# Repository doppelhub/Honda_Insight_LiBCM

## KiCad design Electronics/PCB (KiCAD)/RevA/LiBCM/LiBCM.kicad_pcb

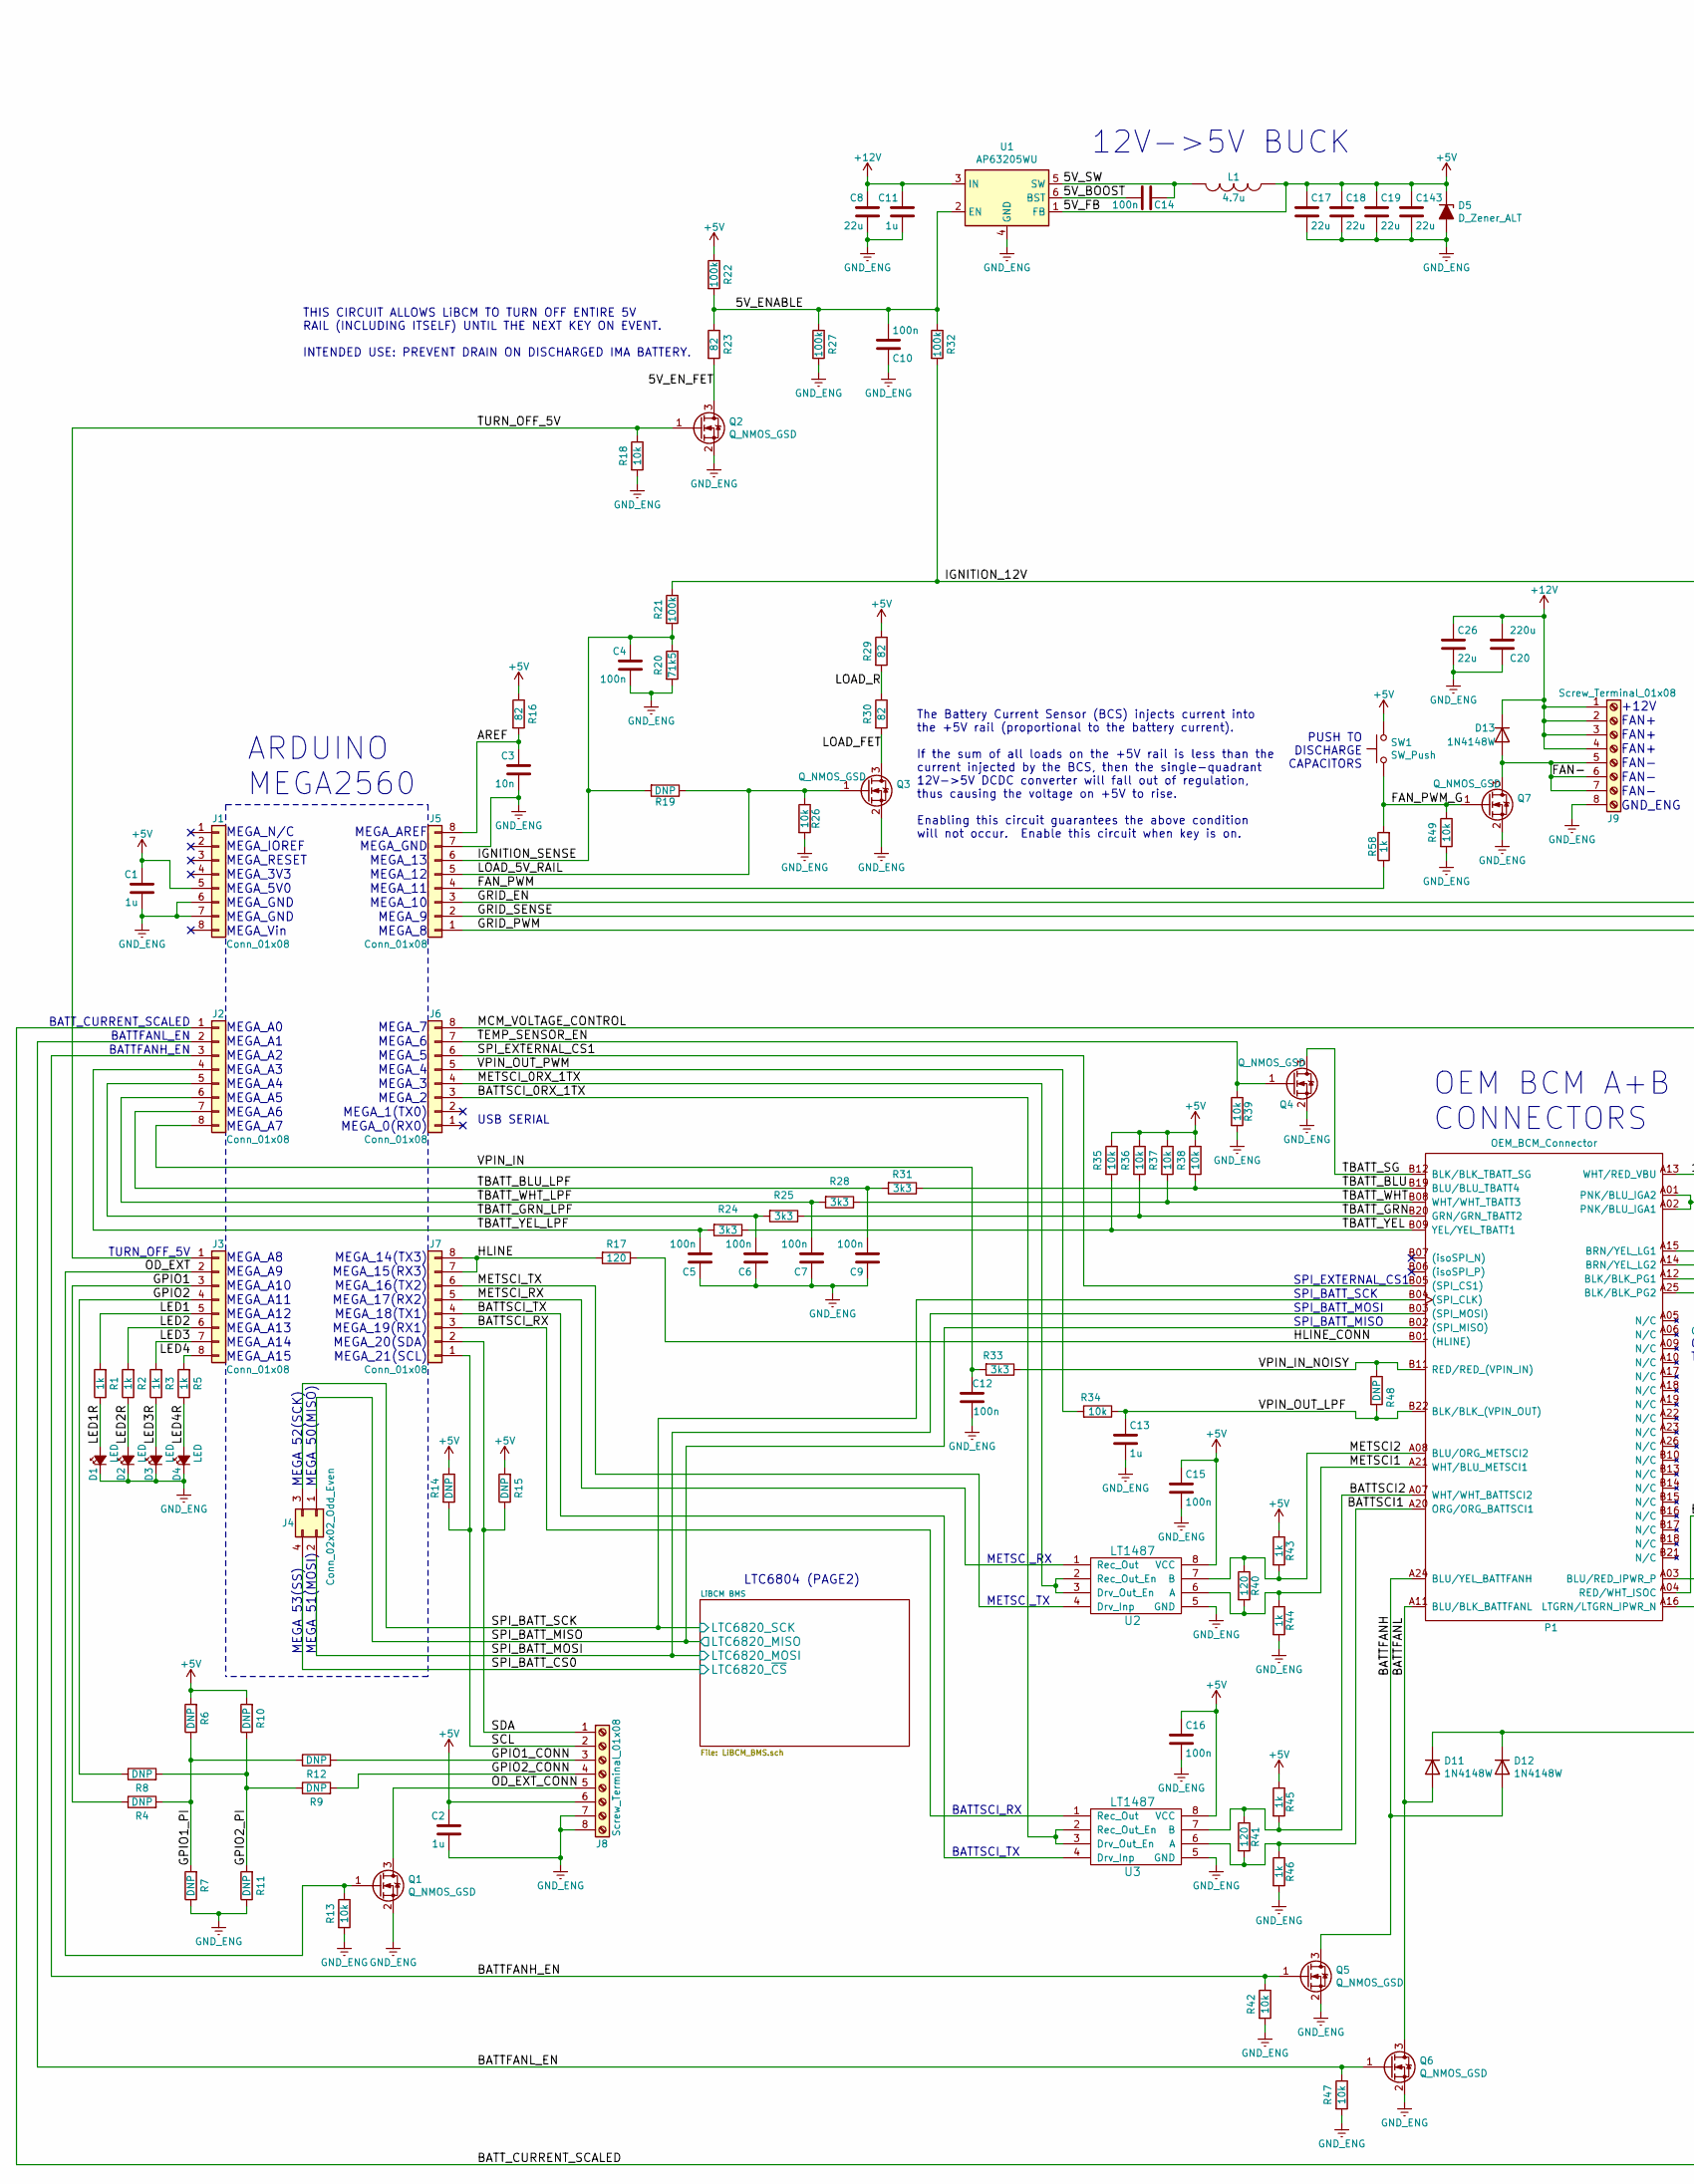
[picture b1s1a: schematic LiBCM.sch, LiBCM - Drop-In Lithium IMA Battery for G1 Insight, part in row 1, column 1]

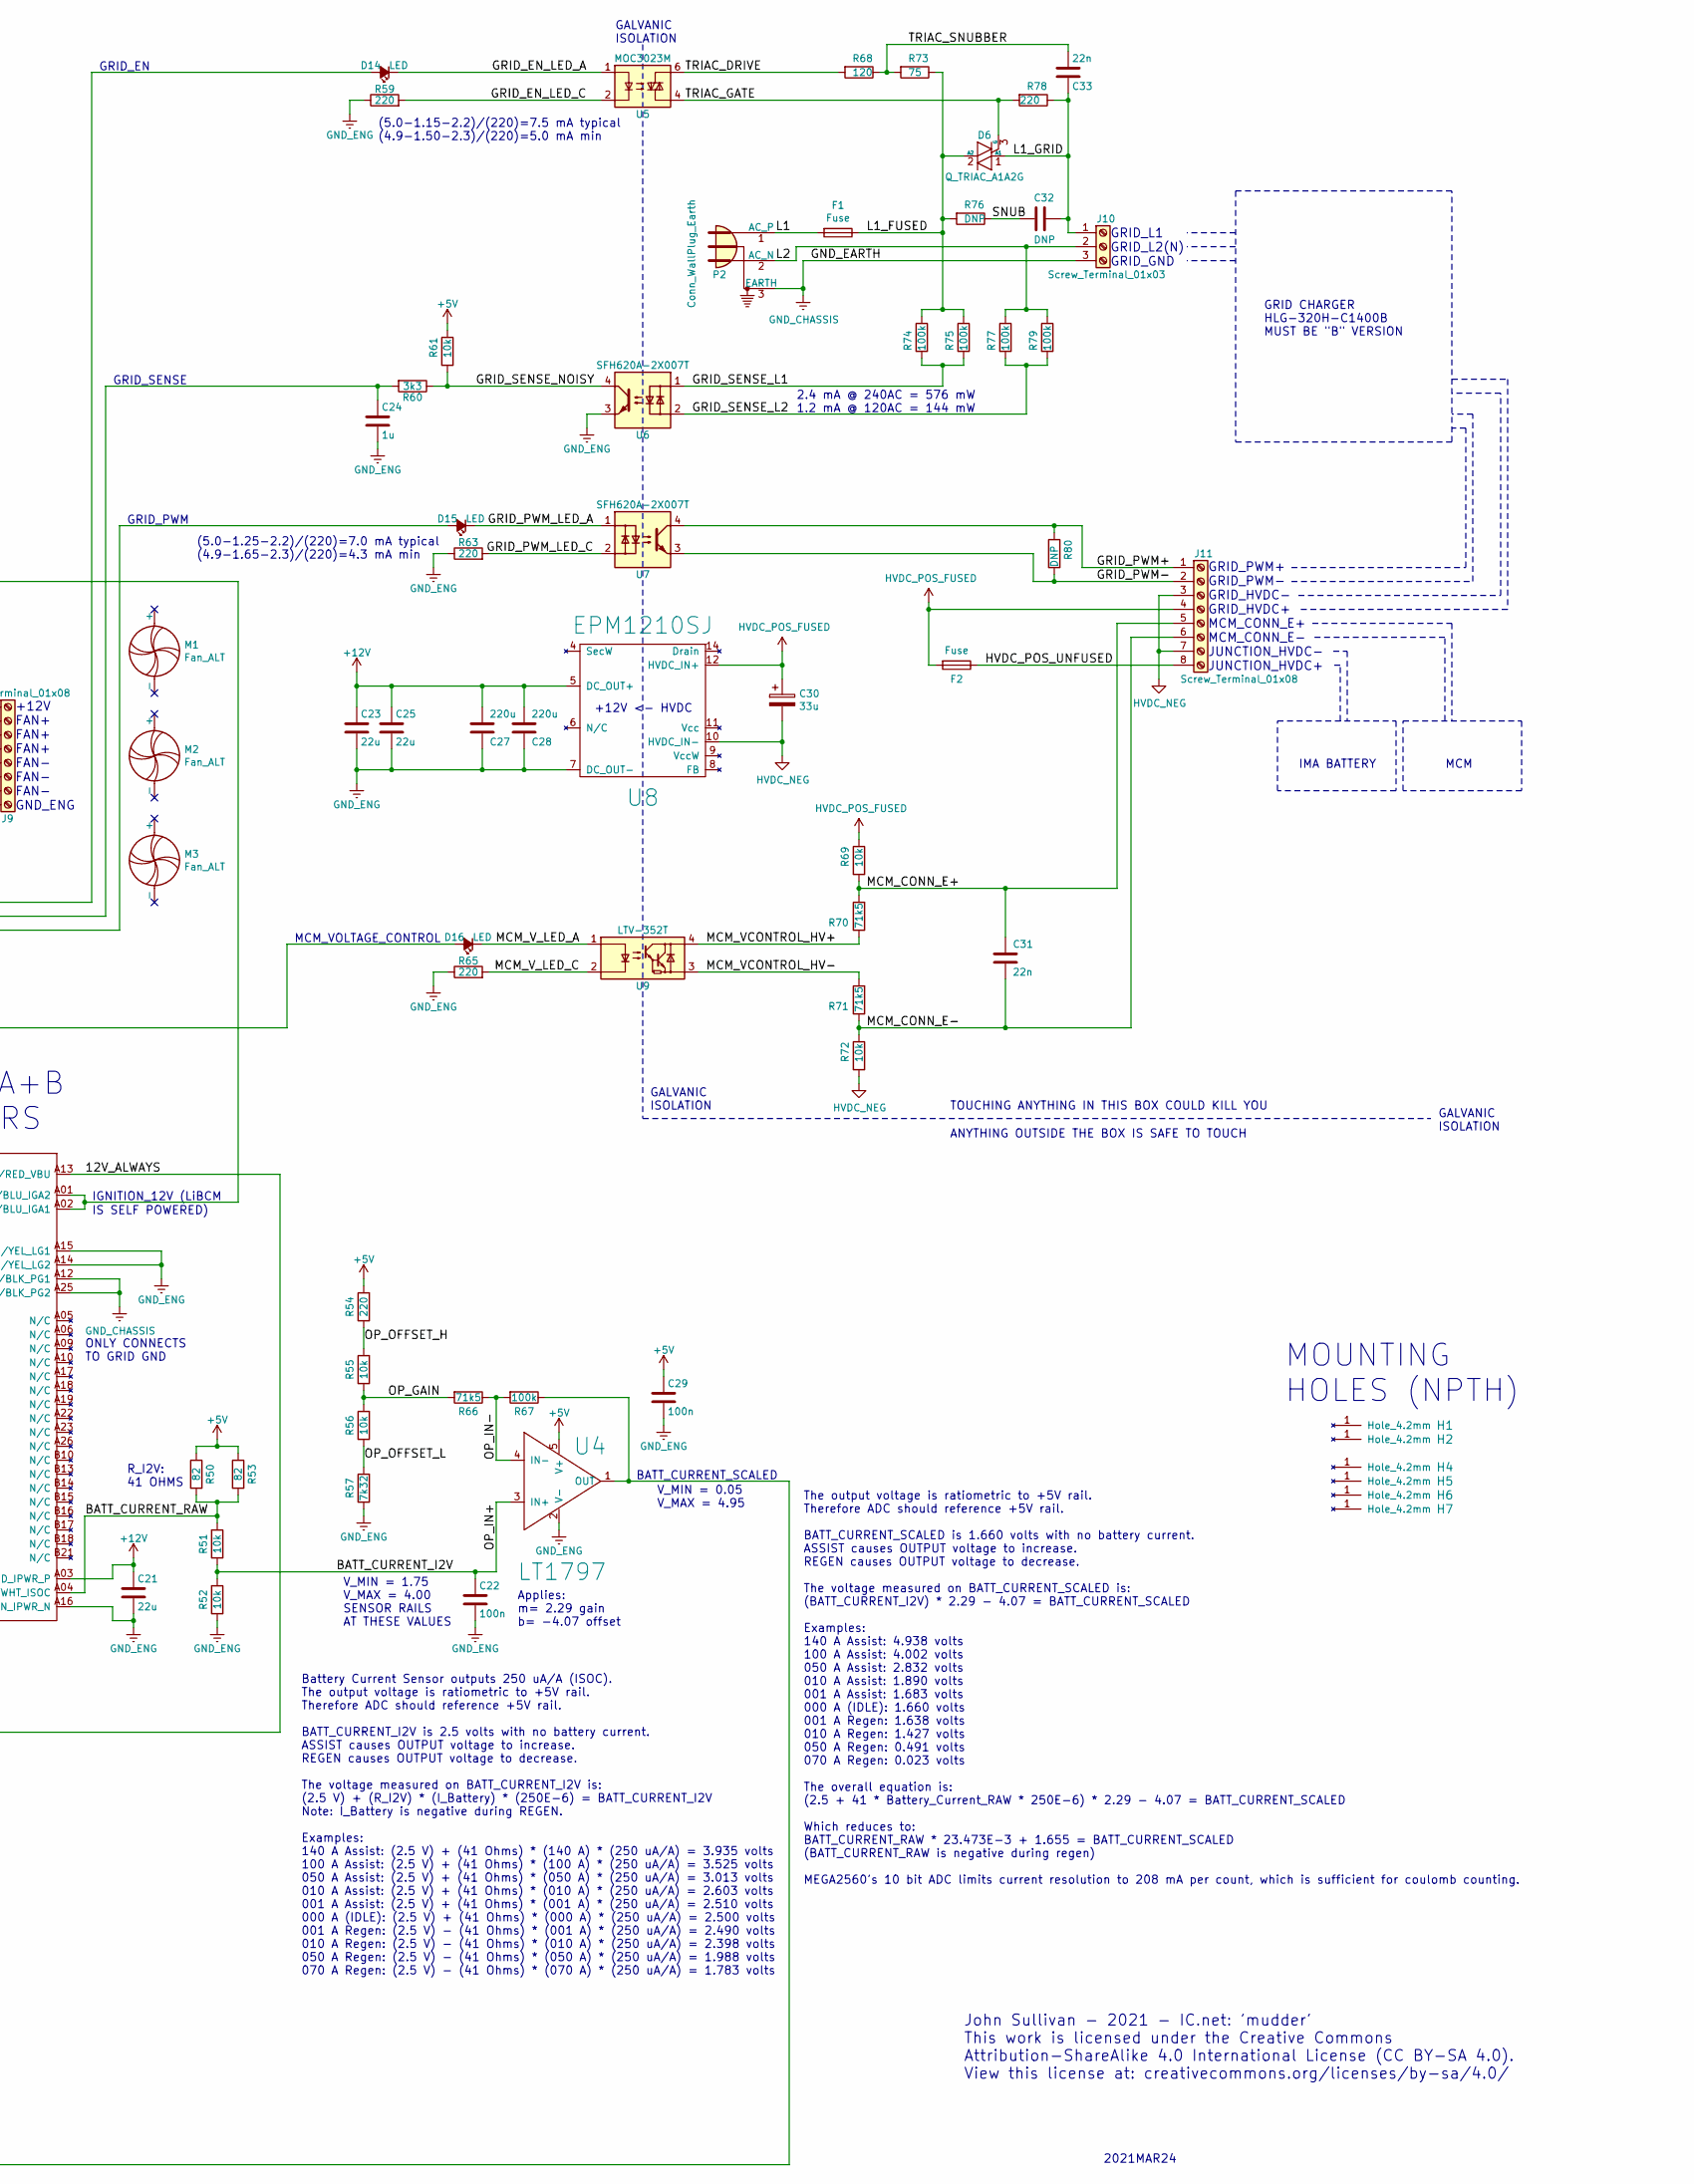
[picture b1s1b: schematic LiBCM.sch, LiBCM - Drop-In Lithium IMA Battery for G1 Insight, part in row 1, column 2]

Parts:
C1, C2, C11, C13, C24: 1u; C_0805_2012Metric
C3: 10n; C_0805_2012Metric
C4, C5, C6, C7, C9, C10, C12, C14, C15, C16, C22, C29: 100n; C_0805_2012Metric
C8, C17, C18, C19, C21, C23, C25, C26, C143: 22u; C_1210_3225Metric
C20, C27, C28: 220u; CP_Elec_10x10
C30: 33u; CP_Radial_D22.0mm_P10.00mm_SnapIn
C31, C33: 22n; C_1206_3216Metric
C32: DNP; C_1206_3216Metric
D1, D2, D3, D4, D14, D15, D16: LED; LED_0805_2012Metric_Castellated
D5: D_Zener_ALT; D_SOD-123
D6: Q_TRIAC_A1A2G; TO-252-3_TabPin2
D11, D12, D13: 1N4148W; D_SOD-123
F1, F2: Fuse; Fuseholder_Cylinder-5x20mm_Schurter_0031_8201_Horizontal_Op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
H1, H2, H4, H5, H6, H7: Hole-4mm2; MountingHole_4.5mm_Pad
J1, J2, J3, J5, J6, J7: Conn_01x08; PinHeader_1x08_P2.54mm_Vertical
J4: Conn_02x02_Odd_Even; PinHeader_2x02_P2.54mm_Vertical
J8, J9, J11: Screw_Terminal_01x08; CONN_1751303
J10: Screw_Terminal_01x03; SolderWire-1sqmm_1x03_P5.4mm_D1.4mm_OD2.7mm
L1: 4.7u; L_TDK_SLF7045
M1, M2, M3: Fan_ALT; FAN_60x60OD_50x50Holes
P1: OEM_BCM_Connector; CONN_BCM_174917-6
P2: Conn_WallPlug_Earth; SolderWire-1sqmm_1x03_P5.4mm_D1.4mm_OD2.7mm
Q1, Q2, Q3, Q4, Q5, Q6, Q7: Q_NMOS_GSD; SOT-23
R1, R2, R3, R5, R43, R44, R45, R46, R58: 1k; R_0805_2012Metric
R4, R6, R7, R8, R9, R10, R11, R12, R14, R15, R19, R48, R80: DNP; R_0805_2012Metric
R13, R18, R26, R34, R35, R36, R37, R38, R39, R42, R47, R49, R51, R52, R55, R56, R61, R69, R72: 10k; R_0805_2012Metric
R16, R23, R29, R30, R50, R53: 82; R_0805_2012Metric
R17, R40, R41, R68: 120; R_0805_2012Metric
R20, R66, R70, R71: 71k5; R_0805_2012Metric
R21, R22, R27, R32, R67, R74, R75, R77, R79: 100k; R_0805_2012Metric
R24, R25, R28, R31, R33, R60: 3k3; R_0805_2012Metric
R54, R59, R63, R65, R78: 220; R_0805_2012Metric
R57: 7k32; R_0805_2012Metric
R73: 75; R_2010_5025Metric
R76: DNP; R_2010_5025Metric
SW1: SW_Push; Panasonic_EVQPUJ_EVQPUA
U1: AP63205WU; TSOT-23-6
U2, U3: LT1487; SOIC-8_5.23x5.23mm_P1.27mm
U4: LT1797; TSOT-23-5
U5: MOC3023M; SMDIP-6_W9.53mm
U6, U7: SFH620A-2X007T; SMDIP-4_W9.53mm_Clearance8mm
U8: EPM1210SJ; DCDC-EPM1210SJ
U9: LTV-352T; SO-4_4.4x3.6mm_P2.54mm

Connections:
+5V: C1.1, C2.1, C15.1, C16.1, C17.1, C18.1, C19.1, C29.1, C143.1, D5.1 (K), J1.5, J8.6, L1.1, R6.2, R10.2, R14.1, R15.2, R16.1, R22.1, R29.1, R35.1, R36.1, R37.1, R38.1, R43.1, R45.1, R50.1, R53.1, R54.2, R61.1, SW1.2, U1.1 (FB), U2.8 (VCC), U3.8 (VCC), U4.5 (V+); also elsewhere on the board
+12V: C8.1, C11.1, C20.1, C21.1, C23.1, C25.1, C26.1, C27.1, C28.1, D13.1 (K), J9.1, J9.2, J9.3, J9.4, P1.A03 (BLU/RED_IPWR_P), U1.3 (IN), U8.5 (DC_OUT+)
/5V_BOOST: C14.2, U1.6 (BST)
/5V_ENABLE: C10.2, R22.2, R23.1, R27.1, R32.1, U1.2 (EN)
/5V_EN_FET: Q2.3 (D), R23.2
/5V_SW: C14.1, L1.2, U1.5 (SW)
/12V_ALWAYS: D11.1 (K), D12.1 (K), P1.A13 (WHT/RED_VBU)
/AREF: C3.1, J5.8, R16.2
/BATTFANH: D12.2 (A), P1.A24 (BLU/YEL_BATTFANH), Q5.3 (D)
/BATTFANH_EN: J2.3, Q5.1 (G), R42.1
/BATTFANL: D11.2 (A), P1.A11 (BLU/BLK_BATTFANL), Q6.3 (D)
/BATTFANL_EN: J2.2, Q6.1 (G), R47.1
/BATTSCI1: P1.A20 (ORG/ORG_BATTSCI1), R41.2, R46.1, U3.6 (A)
/BATTSCI2: P1.A07 (WHT/WHT_BATTSCI2), R41.1, R45.2, U3.7 (B)
/BATTSCI_0RX_1TX: J6.3, U3.2 (Rec_Out_En), U3.3 (Drv_Out_En)
/BATTSCI_RX: J7.3, U3.1 (Rec_Out)
/BATTSCI_TX: J7.4, U3.4 (Drv_Inp)
/BATT_CURRENT_I2V: C22.1, R51.1, R52.2, U4.3 (IN+)
/BATT_CURRENT_RAW: P1.A04 (RED/WHT_ISOC), R50.2, R51.2, R53.2
/BATT_CURRENT_SCALED: J2.1, R67.1, U4.1 (OUT)
/FAN-: D13.2 (A), J9.5, J9.6, J9.7, Q7.3 (D)
/FAN_PWM: J5.4, R58.1
/FAN_PWM_G: Q7.1 (G), R49.1, R58.2, SW1.1
/GPIO1: J3.3, R4.1
/GPIO1_CONN: J8.3, R12.2
/GPIO1_PI: R4.2, R6.1, R7.2, R12.1
/GPIO2: J3.4, R8.1
/GPIO2_CONN: J8.4, R9.2
/GPIO2_PI: R8.2, R9.1, R10.1, R11.2
/GRID_EN: D14.2 (A), J5.3
/GRID_EN_LED_A: D14.1 (K), U5.1
/GRID_EN_LED_C: R59.2, U5.2
/GRID_PWM: D15.2 (A), J5.1
/GRID_PWM+: J11.1, R80.1, U7.4
/GRID_PWM-: J11.2, R80.2, U7.3
/GRID_PWM_LED_A: D15.1 (K), U7.1
/GRID_PWM_LED_C: R63.2, U7.2
/GRID_SENSE: C24.1, J5.2, R60.2
/GRID_SENSE_L1: R74.2, R75.2, U6.1
/GRID_SENSE_L2: R77.2, R79.2, U6.2
/GRID_SENSE_NOISY: R60.1, R61.2, U6.4
/HLINE: J7.7, J7.8, R17.2
/HLINE_CONN: P1.B01 ((HLINE)), R17.1
/HVDC_POS_UNFUSED: F2.1, J11.8
/IGNITION_12V: P1.A01 (PNK/BLU_IGA2), P1.A02 (PNK/BLU_IGA1), R21.1, R32.2
/IGNITION_SENSE: C4.1, J5.6, R19.2, R20.1, R21.2
/L1: F1.2, P2.1 (AC_P)
/L1_FUSED: D6.2 (A2), F1.1, R73.1, R74.1, R75.1, R76.2
/L1_GRID: C32.1, C33.1, D6.1 (A1), J10.1, R78.1
/L2: J10.2, P2.2 (AC_N), R77.1, R79.1
/LED1: J3.5, R1.2
/LED1R: D1.2 (A), R1.1
/LED2: J3.6, R2.2
/LED2R: D2.2 (A), R2.1
/LED3: J3.7, R3.2
/LED3R: D3.2 (A), R3.1
/LED4: J3.8, R5.2
/LED4R: D4.2 (A), R5.1
/LOAD_5V_RAIL: J5.5, Q3.1 (G), R19.1, R26.1
/LOAD_FET: Q3.3 (D), R30.2
/LOAD_R: R29.2, R30.1
/MCM_CONN_E+: C31.2, J11.5, R69.2, R70.2
/MCM_CONN_E-: C31.1, J11.6, R71.1, R72.1
/MCM_VCONTROL_HV+: R70.1, U9.4
/MCM_VCONTROL_HV-: R71.2, U9.3
/MCM_VOLTAGE_CONTROL: D16.2 (A), J6.8
/MCM_V_LED_A: D16.1 (K), U9.1
/MCM_V_LED_C: R65.2, U9.2
/METSCI1: P1.A21 (WHT/BLU_METSCI1), R40.2, R44.1, U2.6 (A)
/METSCI2: P1.A08 (BLU/ORG_METSCI2), R40.1, R43.2, U2.7 (B)
/METSCI_0RX_1TX: J6.4, U2.2 (Rec_Out_En), U2.3 (Drv_Out_En)
/METSCI_RX: J7.5, U2.1 (Rec_Out)
/METSCI_TX: J7.6, U2.4 (Drv_Inp)
/OD_EXT: J3.2, Q1.1 (G), R13.1
/OD_EXT_CONN: J8.5, Q1.3 (D)
/OP_GAIN: R55.1, R56.2, R66.2
/OP_IN-: R66.1, R67.2, U4.4 (IN-)
/OP_OFFSET_H: R54.1, R55.2
/OP_OFFSET_L: R56.1, R57.2
/SCL: J7.1, J8.2, R14.2
/SDA: J7.2, J8.1, R15.1
/SNUB: C32.2, R76.1
/SPI_BATT_CS0: J4.4; also elsewhere on the board
/SPI_BATT_MISO: J4.1, P1.B02 ((SPI_MISO)); also elsewhere on the board
/SPI_BATT_MOSI: J4.2, P1.B03 ((SPI_MOSI)); also elsewhere on the board
/SPI_BATT_SCK: J4.3, P1.B04 ((SPI_CLK)); also elsewhere on the board
/SPI_EXTERNAL_CS1: J6.6, P1.B05 ((SPI_CS1))
/TBATT_BLU: P1.B19 (BLU/BLU_TBATT4), R31.1, R38.2
/TBATT_BLU_LPF: C9.2, J2.7, R31.2
/TBATT_GRN: P1.B20 (GRN/GRN_TBATT2), R25.1, R36.2
/TBATT_GRN_LPF: C6.2, J2.5, R25.2
/TBATT_SG: P1.B12 (BLK/BLK_TBATT_SG), Q4.3 (D)
/TBATT_WHT: P1.B08 (WHT/WHT_TBATT3), R28.1, R37.2
/TBATT_WHT_LPF: C7.2, J2.6, R28.2
/TBATT_YEL: P1.B09 (YEL/YEL_TBATT1), R24.1, R35.2
/TBATT_YEL_LPF: C5.2, J2.4, R24.2
/TEMP_SENSOR_EN: J6.7, Q4.1 (G), R39.1
/TRIAC_DRIVE: R68.2, U5.6
/TRIAC_GATE: D6.3 (G), R78.2, U5.4
/TRIAC_SNUBBER: C33.2, R68.1, R73.2
/TURN_OFF_5V: J3.1, Q2.1 (G), R18.1
/VPIN_IN: C12.1, J2.8, R33.2
/VPIN_IN_NOISY: P1.B11 (RED/RED_(VPIN_IN)), R33.1, R48.1
/VPIN_OUT_LPF: C13.1, P1.B22 (BLK/BLK_(VPIN_OUT)), R34.1, R48.2
/VPIN_OUT_PWM: J6.5, R34.2
GND_CHASSIS: J10.3, P1.A12 (BLK/BLK_PG1), P1.A25 (BLK/BLK_PG2), P2.3 (EARTH)
GND_ENG: C1.2, C2.2, C3.2, C4.2, C5.1, C6.1, C7.1, C8.2, C9.1, C10.1, C11.2, C12.2, C13.2, C15.2, C16.2, C17.2, C18.2, C19.2, C20.2, C21.2, C22.2, C23.2, C24.2, C25.2, C26.2, C27.2, C28.2, C29.2, C143.2, D1.1 (K), D2.1 (K), D3.1 (K), D4.1 (K), D5.2 (A), J1.6, J1.7, J5.7, J8.7, J8.8, J9.8, P1.A14 (BRN/YEL_LG2), P1.A15 (BRN/YEL_LG1), P1.A16 (LTGRN/LTGRN_IPWR_N), Q1.2 (S), Q2.2 (S), Q3.2 (S), Q4.2 (S), Q5.2 (S), Q6.2 (S), Q7.2 (S), R7.1, R11.1, R13.2, R18.2, R20.2, R26.2, R27.2, R39.2, R42.2, R44.2, R46.2, R47.2, R49.2, R52.1, R57.1, R59.1, R63.1, R65.1, U1.4 (GND), U2.5 (GND), U3.5 (GND), U4.2 (V-), U6.3, U8.7 (DC_OUT-); also elsewhere on the board
HVDC_NEG: C30.2, J11.3, J11.7, R72.2, U8.10 (HVDC_IN-)
HVDC_POS_FUSED: C30.1, F2.2, J11.4, R69.1, U8.12 (HVDC_IN+)

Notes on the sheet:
12V->5V BUCK
OEM BCM A+B CONNECTORS
MOUNTING HOLES (NPTH)
2021MAR24
John Sullivan - 2021 - IC.net: 'mudder' This work is licensed under the Creative Commons Attribution-ShareAlike 4.0 International License (CC BY-SA 4.0). View this license at: creativecommons.org/licenses/by-sa/4.0/
+12V FAN+ FAN+ FAN+ FAN- FAN- FAN- GND_ENG
MEGA_N/C MEGA_IOREF MEGA_RESET MEGA_3V3 MEGA_5V0 MEGA_GND MEGA_GND MEGA_Vin
MEGA_A0 MEGA_A1 MEGA_A2 MEGA_A3 MEGA_A4 MEGA_A5 MEGA_A6 MEGA_A7
MEGA_A8 MEGA_A9 MEGA_A10 MEGA_A11 MEGA_A12 MEGA_A13 MEGA_A14 MEGA_A15
MEGA_AREF MEGA_GND MEGA_13 MEGA_12 MEGA_11 MEGA_10 MEGA_9 MEGA_8
MEGA_7 MEGA_6 MEGA_5 MEGA_4 MEGA_3 MEGA_2 MEGA_1(TX0) MEGA_0(RX0)
MEGA_14(TX3) MEGA_15(RX3) MEGA_16(TX2) MEGA_17(RX2) MEGA_18(TX1) MEGA_19(RX1) MEGA_20(SDA) MEGA_21(SCL)
2.4 mA @ 240AC = 576 mW 1.2 mA @ 120AC = 144 mW
GRID_L1 GRID_L2(N) GRID_GND
GRID CHARGER HLG-320H-C1400B MUST BE "B" VERSION
GRID_PWM+ GRID_PWM- GRID_HVDC- GRID_HVDC+ MCM_CONN_E+ MCM_CONN_E- JUNCTION_HVDC- JUNCTION_HVDC+
MCM
IMA BATTERY
GALVANIC ISOLATION
MEGA_53(SS)
IS SELF POWERED)
+12V <- HVDC
The Battery Current Sensor (BCS) injects current into the +5V rail (proportional to the battery current). If the sum of all loads on the +5V rail is less than the current injected by the BCS, then the single-quadrant 12V->5V DCDC converter will fall out of regulation, thus causing the voltage on +5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
R_I2V: 41 OHMS
V_MIN = 1.75 V_MAX = 4.00 SENSOR RAILS AT THESE VALUES
Battery Current Sensor outputs 250 uA/A (ISOC). The output voltage is ratiometric to +5V rail. Therefore ADC should reference +5V rail. BATT_CURRENT_I2V is 2.5 volts with no battery current. ASSIST causes OUTPUT voltage to increase. REGEN causes OUTPUT voltage to decrease. The voltage measured on B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
BATT_CURRENT_SCALED
V_MIN = 0.05 V_MAX = 4.95
Applies: m= 2.29 gain b= -4.07 offset
The output voltage is ratiometric to +5V rail. Therefore ADC should reference +5V rail. BATT_CURRENT_SCALED is 1.660 volts with no battery current. ASSIST causes OUTPUT voltage to increase. REGEN causes OUTPUT voltage to decrease. The voltage measured on BATT_CURRENT_SCALED is: (BATT_CURRENT_I2V) *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
TOUCHING ANYTHING IN THIS BOX COULD KILL YOU
ANYTHING OUTSIDE THE BOX IS SAFE TO TOUCH
IGNITION_12V (LiBCM
THIS CIRCUIT ALLOWS LiBCM TO TURN OFF ENTIRE 5V RAIL (INCLUDING ITSELF) UNTIL THE NEXT KEY ON EVENT. INTENDED USE: PREVENT DRAIN ON DISCHARGED IMA BATTERY.
ONLY CONNECTS TO GRID GND
PUSH TO DISCHARGE CAPACITORS
GRID_EN
GRID_SENSE
GRID_PWM
MCM_VOLTAGE_CONTROL
